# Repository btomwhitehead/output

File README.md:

# output
Simple eurorack dual balanced output module

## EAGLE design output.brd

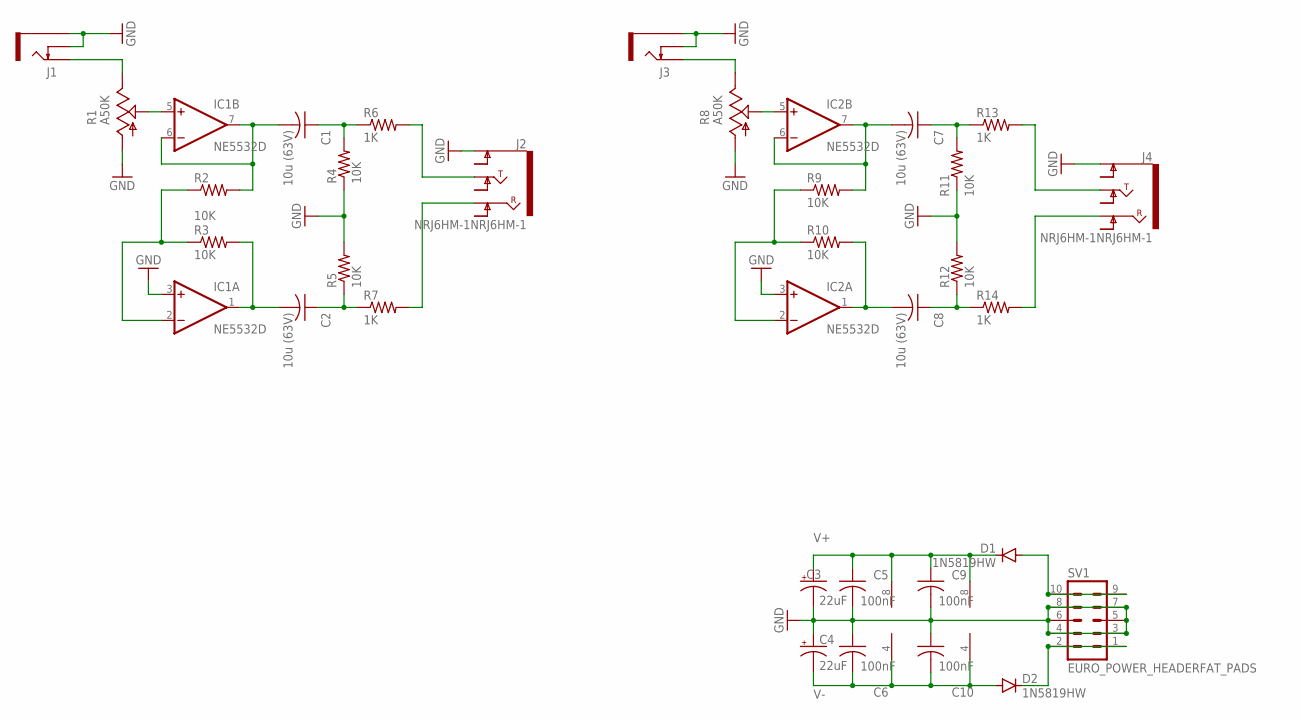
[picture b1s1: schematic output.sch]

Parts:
C1, C2, C7, C8: 10u (63V); C1210
C3, C4: 22uF; PANASONIC_B
C5, C6, C9, C10: 100nF; C0805
D1, D2: 1N5819HW; SOD123
IC1, IC2: NE5532D; SO08
J1, J3: PJ302M
J2, J4: NRJ6HM-1NRJ6HM-1; NRJ6HM-1
R1, R8: A50K; ALPHA_9MM_POT_RIGHT_ANGLE
R2, R3, R4, R5, R9, R10, R11, R12: 10K; R0805
R6, R7, R13, R14: 1K; R0805
SV1: EURO_POWER_HEADERFAT_PADS; EURO_PWR_HEADER_FAT

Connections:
GND: C3.-, C4.+, C5.2, C6.1, C9.2, C10.1, IC1.3 (+IN), IC2.3 (+IN), J1.GND (SLEEVE), J1.SW (SWITCH), J2.SLEEVE (EARTH), J3.GND (SLEEVE), J3.SW (SWITCH), J4.SLEEVE (EARTH), R1.1 (A), R4.1, R5.2, R8.1 (A), R11.1, R12.2, SV1.3, SV1.4, SV1.5, SV1.6, SV1.7, SV1.8
unnamed: IC1.2 (-IN), R2.1, R3.1
unnamed: C2.2, IC1.1 (OUT), R3.2
unnamed: C1.2, IC1.6 (-IN), IC1.7 (OUT), R2.2
unnamed: IC1.5 (+IN), R1.2 (S)
unnamed: C1.1, R4.2, R6.1
unnamed: IC2.5 (+IN), R8.2 (S)
unnamed: C2.1, R5.1, R7.1
unnamed: J1.TIP, R1.3 (E)
unnamed: J2.TIP, R6.2
unnamed: J3.TIP, R8.3 (E)
unnamed: J2.RING, R7.2
unnamed: D1.A, SV1.9, SV1.10
unnamed: C7.1, R11.2, R13.1
unnamed: C8.1, R12.1, R14.1
unnamed: J4.TIP, R13.2
unnamed: J4.RING, R14.2
unnamed: IC2.2 (-IN), R9.1, R10.1
unnamed: C8.2, IC2.1 (OUT), R10.2
unnamed: C7.2, IC2.6 (-IN), IC2.7 (OUT), R9.2
unnamed: D2.C, SV1.1, SV1.2
V+: C3.+, C5.1, C9.1, D1.C, IC1.8 (V+), IC2.8 (V+)
V-: C4.-, C6.2, C10.2, D2.A, IC1.4 (V-), IC2.4 (V-)

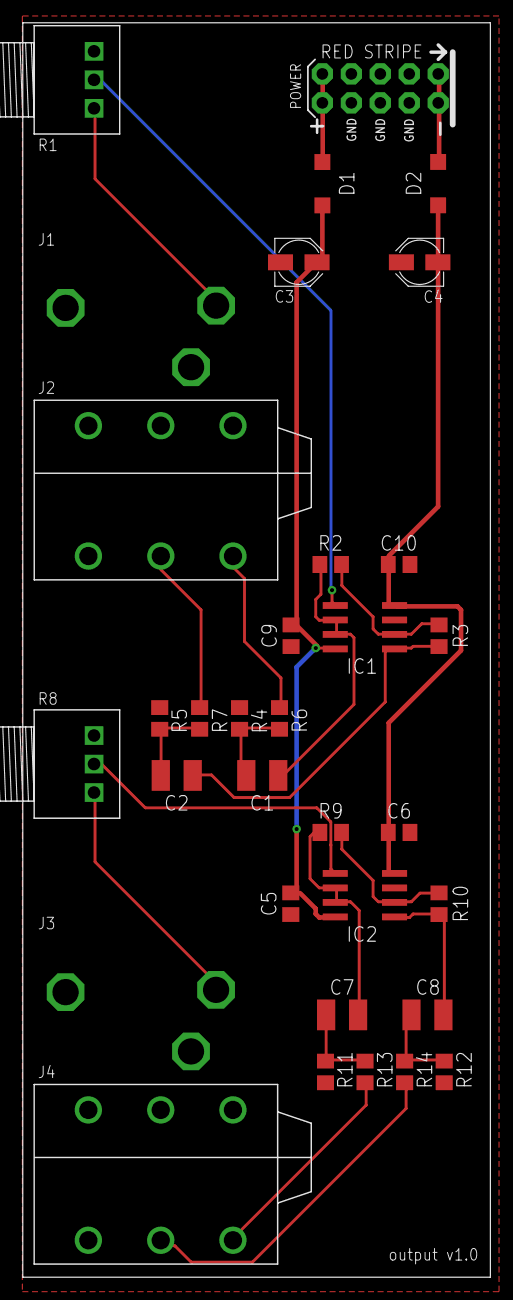
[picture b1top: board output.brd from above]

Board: 2 copper layers, 41.0 x 110.0 mm, 33 parts (0 on the bottom side), 23 nets.

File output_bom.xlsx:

Output, v1.0
Index | Qty | Description | Specs | Value | Package | Ref. Mouser | References
SMT parts
R2, R3, R4, R5, R9, R10, R11, R12 | 8 | Resistor, film | <=0.1% | 10K | 0805 | 603-RE0805BRE0710KL | Yageo RE0805BRE0710KL
R6, R7, R13, R14 | 4 | Resistor, film | <=1% | 1K | 0805 | 603-RC0805FR-071KL | Yageo RC0805FR-071KL
C1, C2, C7, C8 | 4 | Capacitor, ceramic | >= 63V | 10uF | 1210 | 187-CL32B106KMVNNWE | Samsung CL32B106KMVNNWE
C5, C6, C9, C10 | 4 | Capacitor, ceramic | >= 25V | 100nF | 0805 | 81-GRM21BR72A104KA4K | Murata GRM21BR72A104KAC4K
C3, C4 | 2 | Capacitor, electrolytic | >= 25V | 22uF | Panasonic B | 647-UCM1V220MCL1GS | Nichicon UCM1V220MCL1GS
D1, D2 | 2 | 1N5819HW diode |  | 1N5819HW | SOD123 | 621-1N5819HW-F | Diodes Inc 1N5819HW-7-F
IC1, IC2 | 2 | NE5532 dual opamp |  | NE5532D | SOIC8 | 595-NE5532D | Texas Instruments NE5532D
R1, R8 | 2 | Alpha 9mm right angle potentiometer |  | A50K |  |  | Alpha right angle 9mm: https://www.thonk.co.uk/shop/alpha-right-angle-t18/
SV1 | 1 | 2x5 male header, 2.54mm pitch |  |  |  | 649-1012938191002BLF | Amphenol 10129381-910002BLF
J2, J4 | 2 | Neutrik NRJ6HM-1 |  |  |  | 568-NRJ6HM1 | Neutrik NRJ6HM-1
 | 2 | Neutrik NRJ6HM-1 nut |  |  |  | 568-NRJ-NUT-MN | Neutrik NRJ-NUT-MN
J1, J3 | 2 | PJ302M right angle 3.5 mm jack socket |  |  |  |  | PJ302M: https://www.thonk.co.uk/shop/3-5mm-jacks/

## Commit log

2022-09-17 Added hardware files v1.0
